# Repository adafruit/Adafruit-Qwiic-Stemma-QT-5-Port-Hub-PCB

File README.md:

## Adafruit Qwiic / Stemma QT 5 Port Hub PCB

<a href="http://www.adafruit.com/products/5625"><br/>
Click here to purchase one from the Adafruit shop</a>

PCB files for the Adafruit Qwiic / Stemma QT 5 Port Hub. 

Format is EagleCAD schematic and board layout
* https://www.adafruit.com/product/5625

### Description

Qwiic, or STEMMA QT, is a very efficient way to quickly prototype an idea, but a lot of Qwiic/Stemma QT driver boards only have one port, and devices have two ports but that's only good for chaining. Maybe you want to reduce your I2C line capacitance by having a star formation instead of a looooong chain. Or maybe its just easier for your mechanical layout to have them closer to a central point. 

This 5-Port Passive Hub board has 5 vertical JST SH 1mm connectors in a row, all with the power, ground and SDA/SCL pins connected. There's also breadboard breakout pins if you need. Use this hub to add as many I2C devices to the bus as you need. Complete with mounting holes so the board can be added to any system. A small power LED lets you know that the hub board has connectivity.

Please note: this is a 'passive' hub, so it isn't like you can connect 5 of the same-address-sensor-boards and have them individually work. It's only a mechanical assistant for connecting many QT/Qwiic boards together.

Simply plug and go. No soldering required, but comes with a bit of header if you prefer breadboarding.

### License

Adafruit invests time and resources providing this open source design, please support Adafruit and open-source hardware by purchasing products from [Adafruit](https://www.adafruit.com)!

Designed by Limor Fried/Ladyada for Adafruit Industries.

Creative Commons Attribution/Share-Alike, all text above must be included in any redistribution. 
See license.txt for additional details.

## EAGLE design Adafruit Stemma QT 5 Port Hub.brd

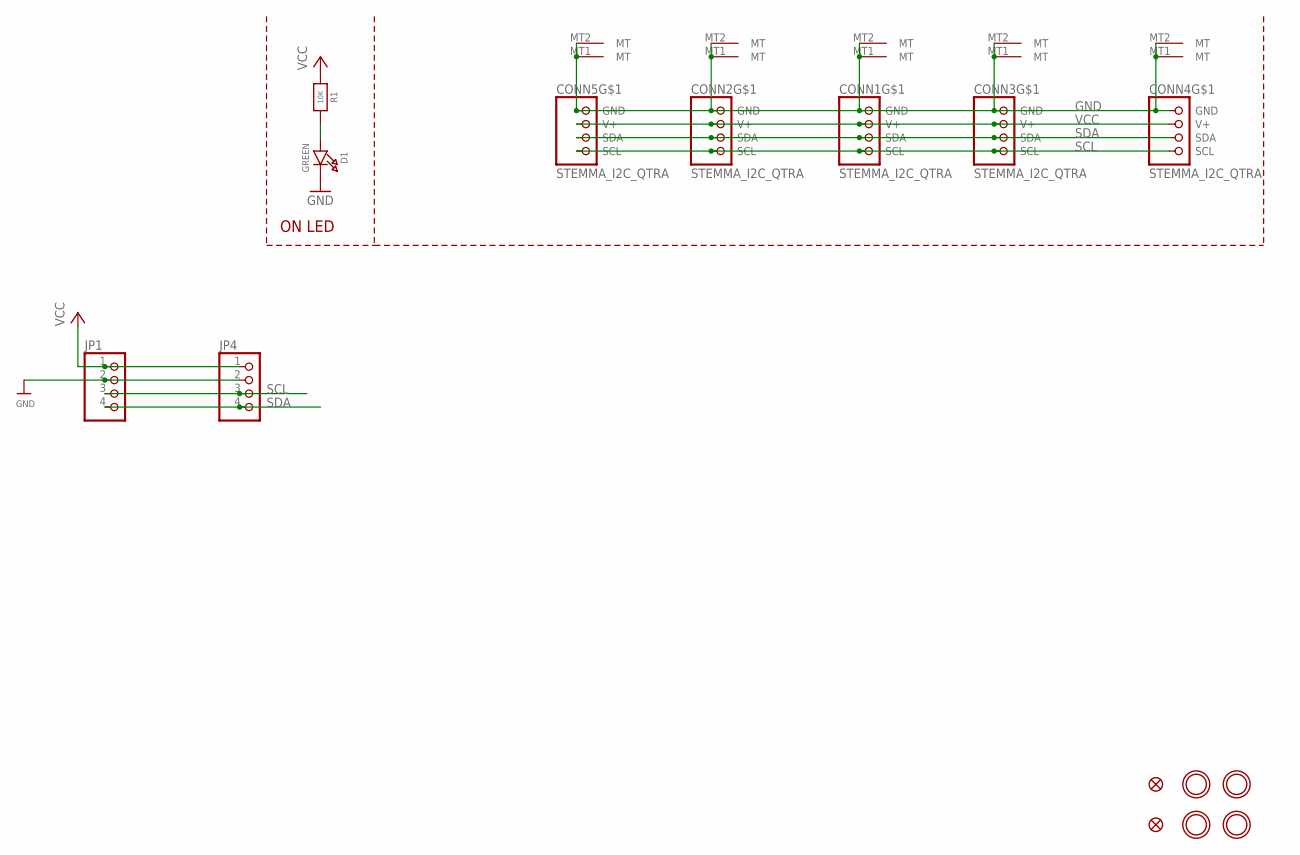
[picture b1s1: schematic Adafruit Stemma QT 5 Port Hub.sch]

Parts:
CONN1, CONN2, CONN3, CONN4, CONN5: STEMMA_I2C_QTRA; JST_SH4_RA
D1: GREEN; CHIPLED_0603_NOOUTLINE
FID3, FID4: FIDUCIAL_1MM
JP1, JP4: HEADER-1X476MIL; 1X04_ROUND_76
R1: 10K; 0603-NO
U$1, U$17, U$19, U$21: MOUNTINGHOLE2.5; MOUNTINGHOLE_2.5_PLATED

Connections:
GND: CONN1.1 (GND), CONN1.MT1 (MT), CONN1.MT2 (MT), CONN2.1 (GND), CONN2.MT1 (MT), CONN2.MT2 (MT), CONN3.1 (GND), CONN3.MT1 (MT), CONN3.MT2 (MT), CONN4.1 (GND), CONN4.MT1 (MT), CONN4.MT2 (MT), CONN5.1 (GND), CONN5.MT1 (MT), CONN5.MT2 (MT), D1.C, JP1.2, JP4.2
unnamed: D1.A, R1.2
SCL: CONN1.4 (SCL), CONN2.4 (SCL), CONN3.4 (SCL), CONN4.4 (SCL), CONN5.4 (SCL), JP1.3, JP4.3
SDA: CONN1.3 (SDA), CONN2.3 (SDA), CONN3.3 (SDA), CONN4.3 (SDA), CONN5.3 (SDA), JP1.4, JP4.4
VCC: CONN1.2 (V+), CONN2.2 (V+), CONN3.2 (V+), CONN4.2 (V+), CONN5.2 (V+), JP1.1, JP4.1, R1.1

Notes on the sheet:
ON LED

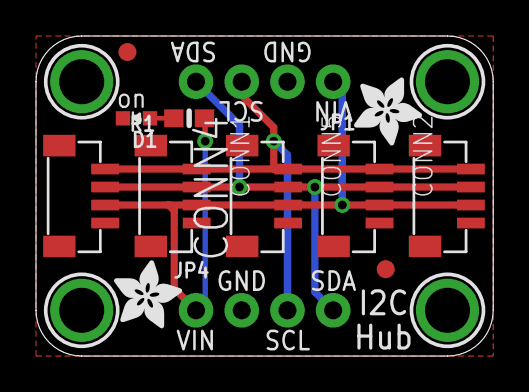
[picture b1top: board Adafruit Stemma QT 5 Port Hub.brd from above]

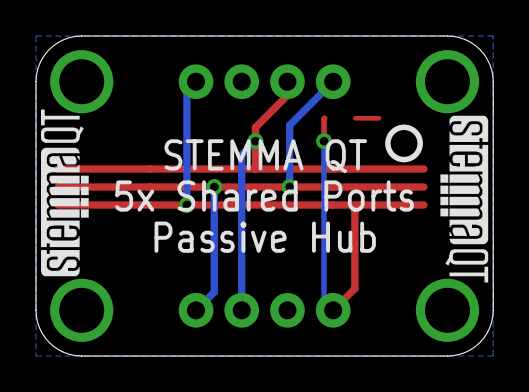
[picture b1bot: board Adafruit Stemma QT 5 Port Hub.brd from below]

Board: 2 copper layers, 25.4 x 17.8 mm, 20 parts (3 on the bottom side), 5 nets.

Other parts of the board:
U$2, U$3: ADAFRUIT_3.5MM
U$25: PCBFEAT-REV-040
U$30, U$31: STEMMAQT

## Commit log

2022-09-22 Adding cookiecutter output
2022-09-22 Updating readme
2022-09-22 Updating image

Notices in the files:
parts and their libraries:
microbuilder: This work is placed in the public domain, and may be freely used for commercial and non-commercial work with the following conditions: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
